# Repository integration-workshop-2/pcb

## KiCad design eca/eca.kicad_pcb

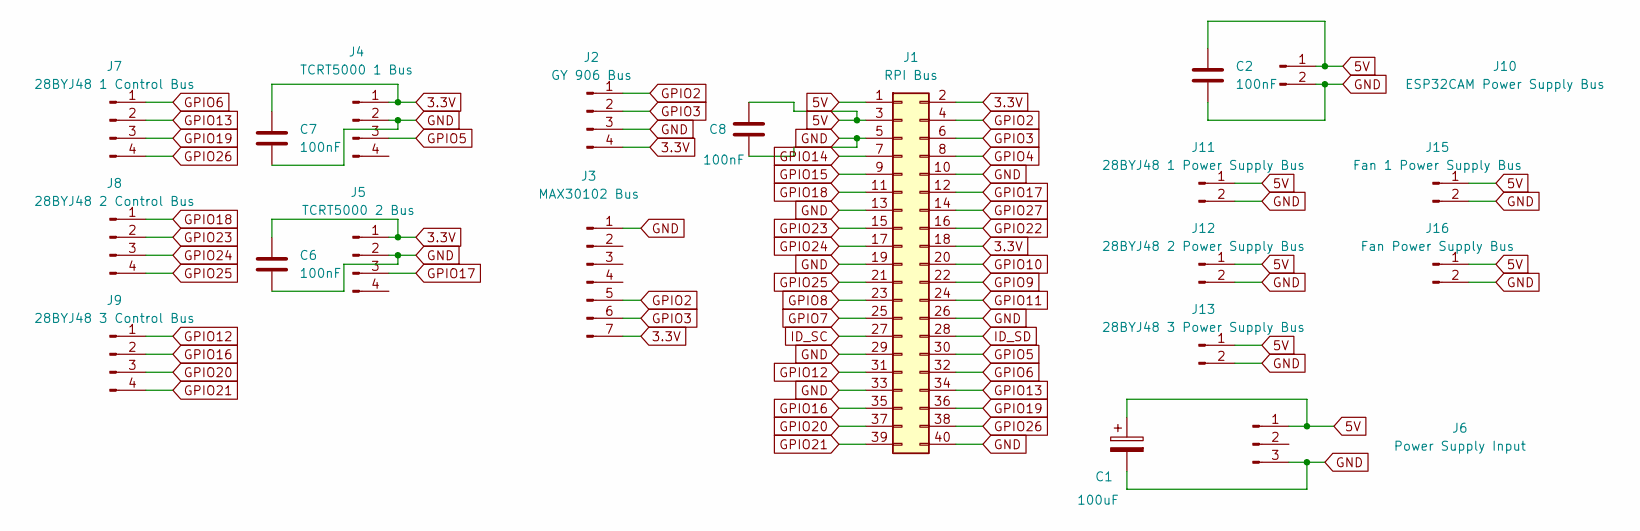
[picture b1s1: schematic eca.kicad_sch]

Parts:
C1: 100uF; CP_Radial_D8.0mm_P5.00mm
C2, C6, C7, C8: 100nF; C_Disc_D4.3mm_W1.9mm_P5.00mm
J1: RPI Bus; PinHeader_2x20_P2.54mm_Vertical
J2: GY 906 Bus; PinHeader_1x04_P2.54mm_Vertical
J3: MAX30102 Bus; PinHeader_1x07_P2.54mm_Vertical
J4: TCRT5000 1 Bus; PinHeader_1x04_P2.54mm_Vertical
J5: TCRT5000 2 Bus; PinHeader_1x04_P2.54mm_Vertical
J6: Power Supply Input; TerminalBlock_Xinya_XY308-2.54-3P_1x03_P2.54mm_Horizontal
J7: 28BYJ48 1 Control Bus; PinHeader_1x04_P2.54mm_Vertical
J8: 28BYJ48 2 Control Bus; PinHeader_1x04_P2.54mm_Vertical
J9: 28BYJ48 3 Control Bus; PinHeader_1x04_P2.54mm_Vertical
J10: ESP32CAM Power Supply Bus; PinHeader_1x02_P2.54mm_Vertical
J11: 28BYJ48 1 Power Supply Bus; PinHeader_1x02_P2.54mm_Vertical
J12: 28BYJ48 2 Power Supply Bus; PinHeader_1x02_P2.54mm_Vertical
J13: 28BYJ48 3 Power Supply Bus; PinHeader_1x02_P2.54mm_Vertical
J15: Fan 1 Power Supply Bus; PinHeader_1x02_P2.54mm_Vertical
J16: Fan Power Supply Bus; PinHeader_1x02_P2.54mm_Vertical

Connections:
3.3V: C6.1, C7.1, J1.2, J1.18, J2.4, J3.7, J4.1, J5.1
5V: C1.1, C2.1, C8.1, J1.1, J1.3, J6.1, J10.1, J11.1, J12.1, J13.1, J15.1, J16.1
GND: C1.2, C2.2, C6.2, C7.2, C8.2, J1.5, J1.10, J1.13, J1.19, J1.26, J1.29, J1.33, J1.40, J2.3, J3.1, J4.2, J5.2, J6.3, J10.2, J11.2, J12.2, J13.2, J15.2, J16.2
GPIO2: J1.4, J2.1, J3.5
GPIO3: J1.6, J2.2, J3.6
GPIO4: J1.8
GPIO5: J1.30, J4.3
GPIO6: J1.32, J7.1
GPIO7: J1.25
GPIO8: J1.23
GPIO9: J1.22
GPIO10: J1.20
GPIO11: J1.24
GPIO12: J1.31, J9.1
GPIO13: J1.34, J7.2
GPIO14: J1.7
GPIO15: J1.9
GPIO16: J1.35, J9.2
GPIO17: J1.12, J5.3
GPIO18: J1.11, J8.1
GPIO19: J1.36, J7.3
GPIO20: J1.37, J9.3
GPIO21: J1.39, J9.4
GPIO22: J1.16
GPIO23: J1.15, J8.2
GPIO24: J1.17, J8.3
GPIO25: J1.21, J8.4
GPIO26: J1.38, J7.4
GPIO27: J1.14
ID_SC: J1.27
ID_SD: J1.28

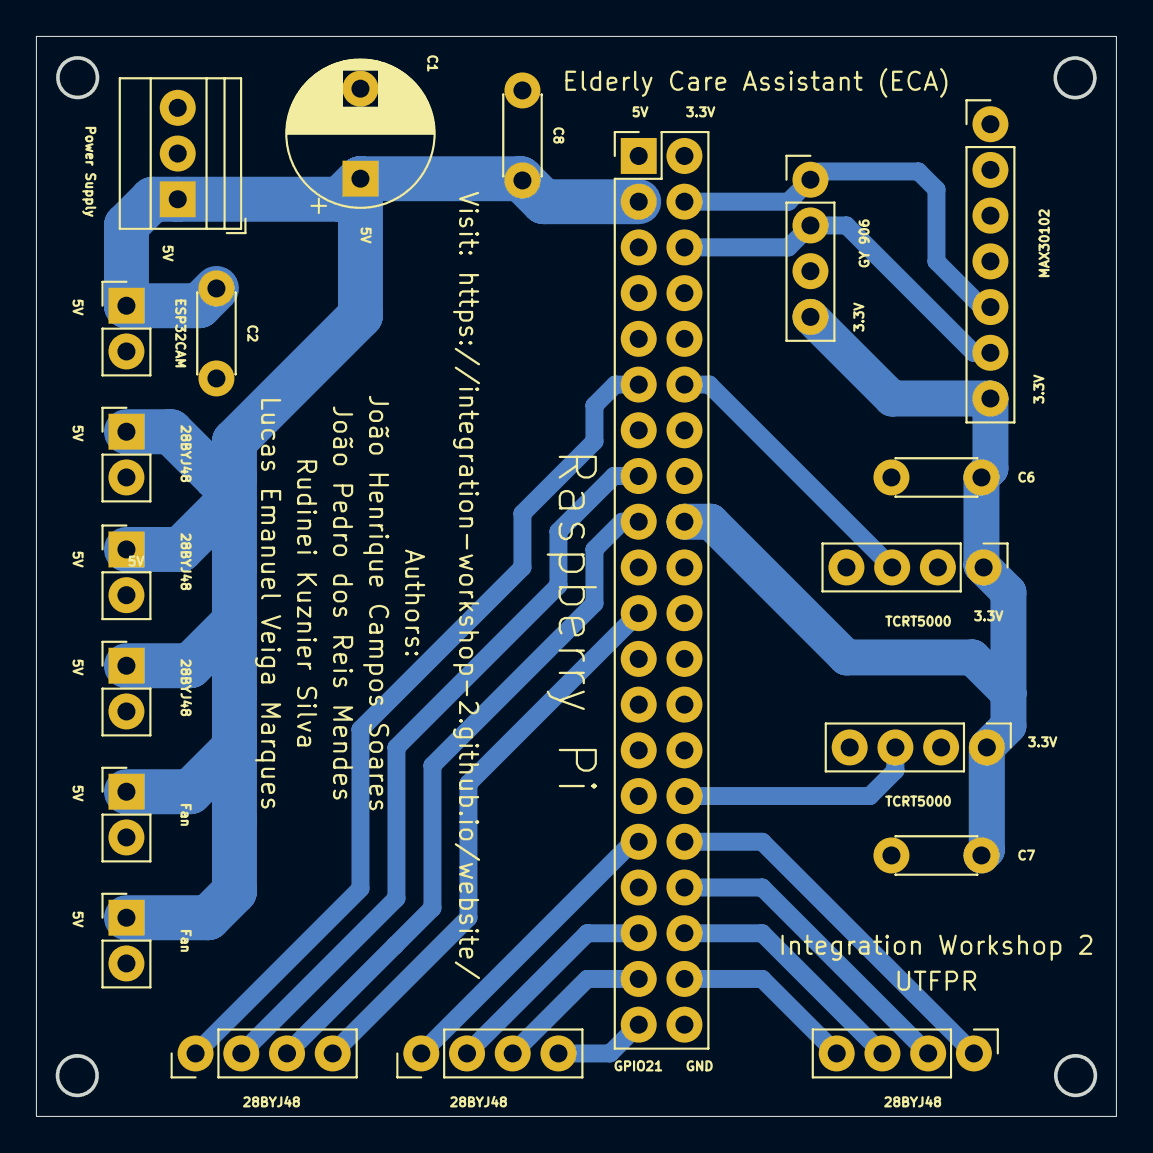
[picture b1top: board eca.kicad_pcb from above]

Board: 2 copper layers, 59.9 x 59.9 mm, 20 parts (0 on the bottom side), 19 nets.

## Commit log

2024-12-07 modified pads and tracks sizes
2024-12-07 added fan bus
2024-12-07 removed unused files
2024-12-07 changed input connector
2024-12-08 changed power supply connector
2024-12-09 updated gerber and drill files
2024-12-13 alpha version
